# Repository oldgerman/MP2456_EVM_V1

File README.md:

# MP2456 评估板 V1.0 

## PCB

## B.O.M

| NAME | VALUE        | PACKAGE  |
| ---- | ------------ | -------- |
| C2   | 0.1uF        | 0603     |
| C3   | 10uF/25V     | 0805     |
| C4   | 0.1uF/50V    | 0603     |
| C5   | 47pF         | 0603     |
| C6   | 10uF/50V     | 1206     |
| C8   | 0.1uF/50V    | 0603     |
| D1   | DSK16 60V/1A | SOD123   |
| D2   | 1N4148       | SOD123   |
| J1   | CONN_1X4     | 2.54mm   |
| L1   | 10uH         | 4020TYPE |
| R1   | 500k         | 0603     |
| R2   | NS           | 0603     |
| R3   | 0R           | 0603     |
| R5   | 124k         | 0603     |
| R6   | 23.7k        | 0603     |
| R9   | 0R           | 0603     |
| U1   | MP2456       | SOT23-6  |

## 参数

典型输出5V/0.5A, 建议输入电压8-50V，开关频率1.2MHz

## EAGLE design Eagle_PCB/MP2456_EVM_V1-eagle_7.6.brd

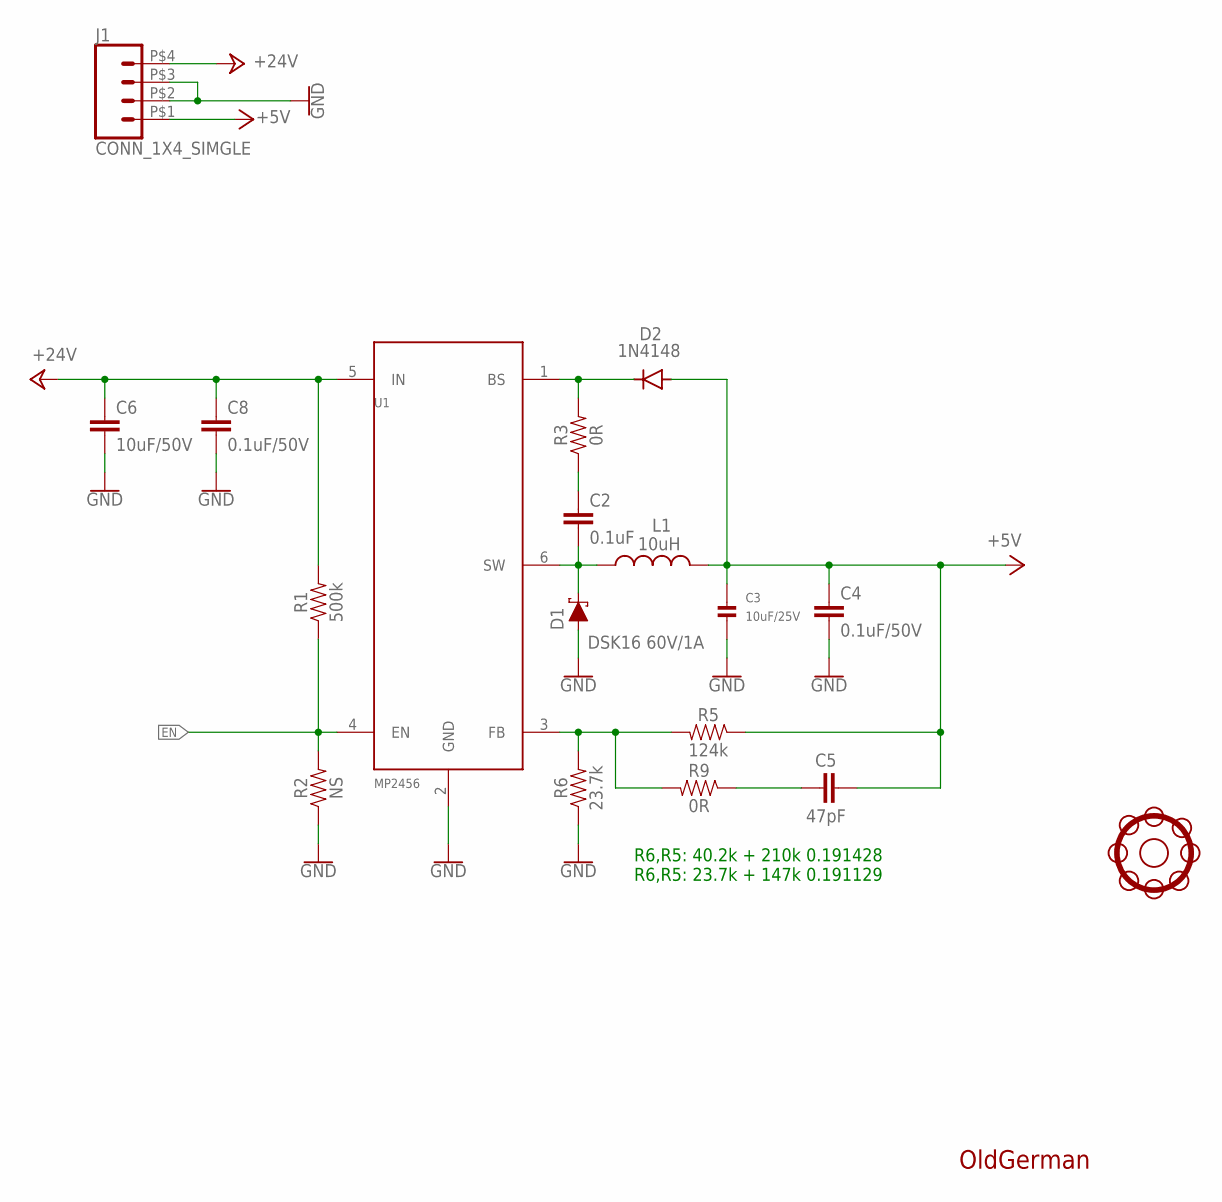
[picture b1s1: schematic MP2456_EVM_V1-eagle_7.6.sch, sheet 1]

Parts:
C2: 0.1uF; 0603
C3: 10uF/25V; _0805MP
C4, C8: 0.1uF/50V; 0603
C5: 47pF; 0603
C6: 10uF/50V; 1206
D1: DSK16 60V/1A; SOD123
D2: 1N4148; SOD123
J1: CONN_1X4_SIMGLE; CONN_1X04_SINGLE
L1: 10uH; 4020TYPE
R1: 500k; 0603
R2: NS; 0603
R3, R9: 0R; 0603
R5: 124k; 0603
R6: 23.7k; 0603
U1: MP2456; SOT23-6
U$1: SUN_HOLE_M3

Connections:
+5V: C3.1, C4.1, C5.2, D2.A, J1.P$1 (1), L1.P$2 (2), R5.1
+24V: C6.1, C8.1, J1.P$4 (4), R1.2, U1.5 (IN)
BS: D2.C, R3.2, U1.1 (BS)
EN: R1.1, R2.2, U1.4 (EN)
GND: C3.2, C4.2, C6.2, C8.2, D1.A, J1.P$2 (2), J1.P$3 (3), R2.1, R6.1, U1.2 (GND)
unnamed: C2.1, R3.1
unnamed: R5.2, R6.2, R9.2, U1.3 (FB)
unnamed: C5.1, R9.1
SW: C2.2, D1.C, L1.P$1 (1), U1.6 (SW)

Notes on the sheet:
OldGerman
R6,R5: 40.2k + 210k 0.191428 R6,R5: 23.7k + 147k 0.191129

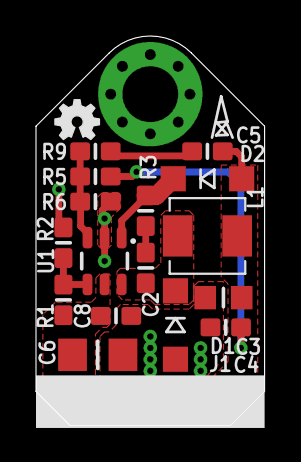
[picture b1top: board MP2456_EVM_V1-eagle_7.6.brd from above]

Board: 2 copper layers, 12.7 x 21.6 mm, 20 parts (1 on the bottom side), 9 nets.

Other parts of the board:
U$3, U$4: OSHW-LOGO-MINI

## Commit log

2020-06-29 MP2456_EVM_V1
2020-08-05 增加了Eagle7.X版本

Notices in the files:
parts and their libraries:
SparkFun-Capacitors: Licensing: Creative Commons ShareAlike 4.0 International - https://creativecommons.org/licenses/by-sa/4.0
microbuilder: This work is placed in the public domain, and may be freely used for commercial and non-commercial work with the following conditions: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
